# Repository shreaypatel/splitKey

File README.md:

# Ataraxia - Custom 50% Split Keyboard

### Description
Ataraxia is a wireless 52-key, 3D printed ergonomic keyboard desinged for a focused typing experience. The board is powered by dual Seeed Studio XIAO nRF52840 microcontrollers running ZMK firmware. 
It utilizes Bluetooth 5.0 to communicate seamlessly without a cable connecting the halves. The hardware stack includes a custom-routed printed circuit board, Kailh MX hotswap sockets, and direct-wired 
350mAh LiPo batteries for extended operational life.

This project was designed to create an open source, minimalist workspace that promotes ergonomic health withouting compromising functionality. Beyond the physical utility, it serves as a 
comprehensive hardware engineering exercise. Building this keyboard helped me learn engineering design, CAD modeling, PCB routing, soldering, and embedded firmware compilation. Check out the web app to learn touch typing on this split keyboard layout here: https://ataraxiatype.netlify.app/

3D Model

*Full mechanical assembly modeled in Onshape.*

Custom PCB

*Custom PCB designed and routed in KiCad.*

Wiring Diagram

*Simplified direct-wiring diagram connecting the 3.7V LiPo battery to the XIAO nRF52840.*

Bill of Materials (BOM)
[Click here to view the full Bill of Materials (CSV)](<BOM/splitkeyBOM - Sheet1.csv>)

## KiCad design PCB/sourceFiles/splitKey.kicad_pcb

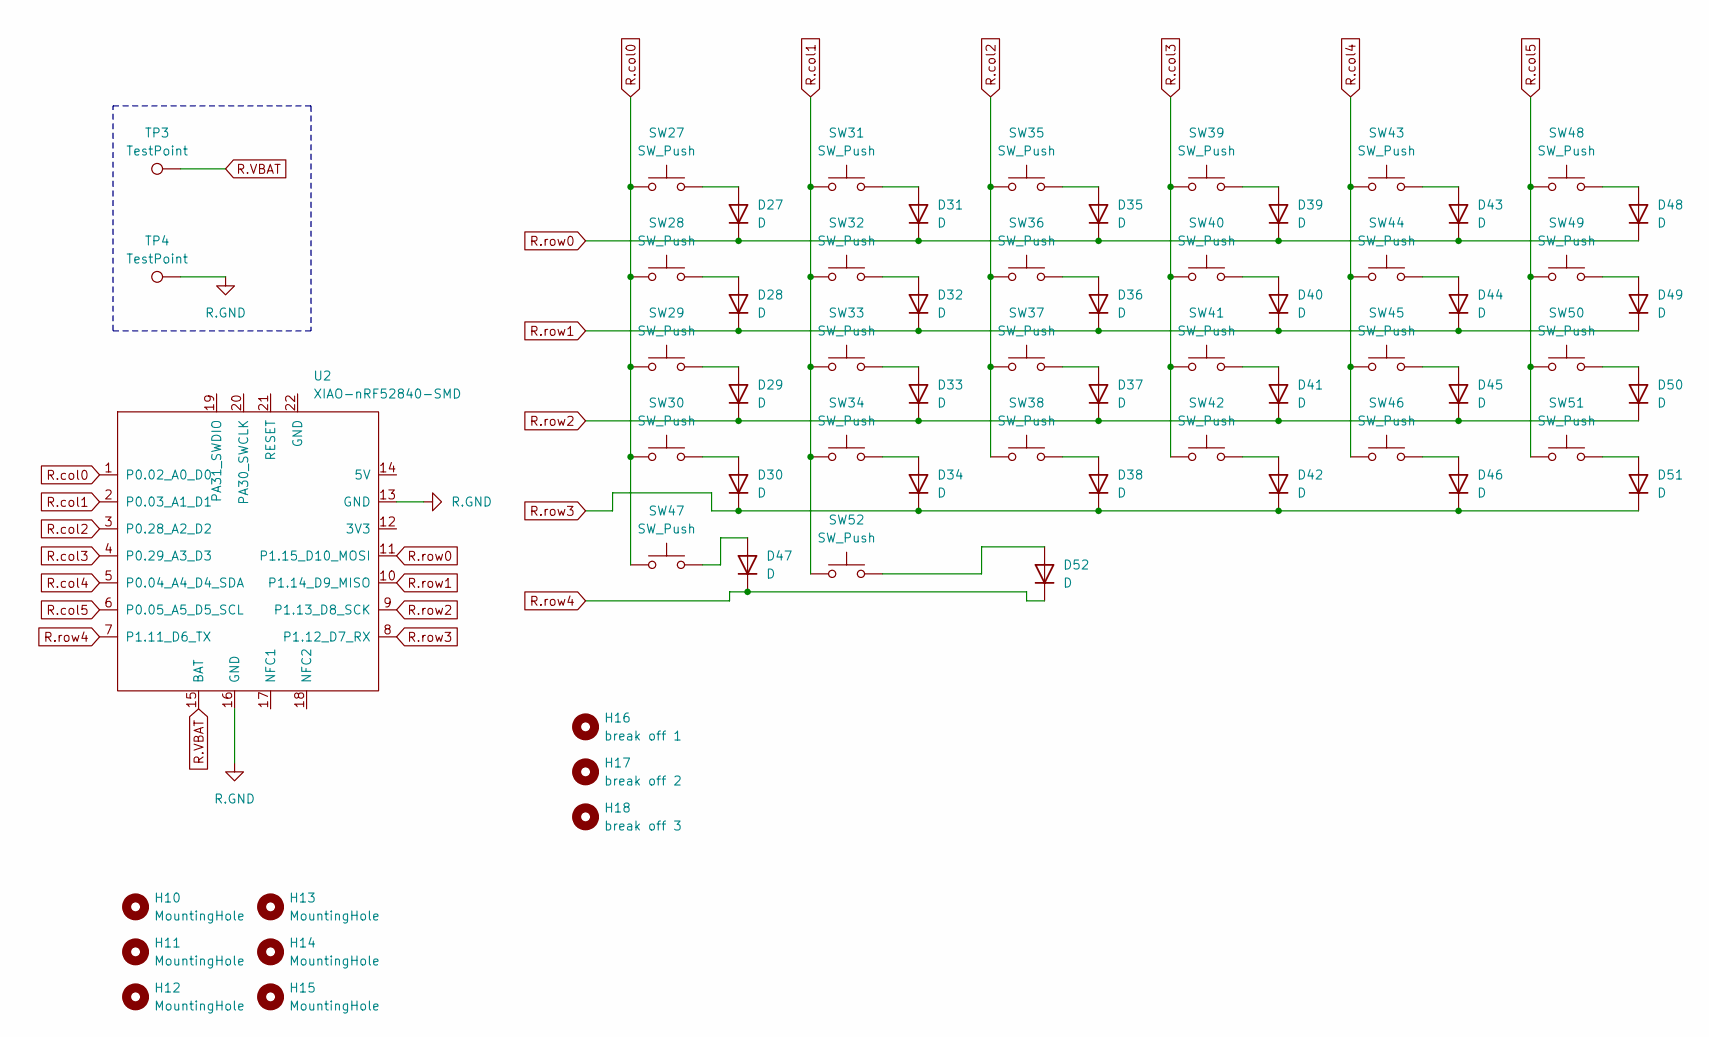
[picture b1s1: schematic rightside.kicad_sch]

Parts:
D27, D28, D29, D30, D31, D32, D33, D34, D35, D36, D37, D38, D39, D40, D41, D42, D43, D44, D45, D46, D47, D48, D49, D50, D51, D52: D; D_SOD-123
H10, H11, H12, H13, H14, H15: MountingHole; MountingHole_2.2mm_M2
H16: break off 1; mouse-bite-5mm-slot
H17: break off 2; mouse-bite-5mm-slot
H18: break off 3; mouse-bite-5mm-slot
SW27, SW28, SW29, SW30, SW31, SW32, SW33, SW34, SW35, SW36, SW37, SW38, SW39, SW40, SW41, SW42, SW43, SW44, SW45, SW46, SW47, SW48, SW49, SW50, SW51, SW52: SW_Push; MX_Hotswap_1.00u
TP3, TP4: TestPoint; TestPoint_Pad_D2.0mm
U2: XIAO-nRF52840-SMD; modified-XIAO-nRF52840-SMD

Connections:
unnamed: D27.2 (A), SW27.2
unnamed: D28.2 (A), SW28.2
unnamed: D29.2 (A), SW29.2
unnamed: D30.2 (A), SW30.2
unnamed: D31.2 (A), SW31.2
unnamed: D32.2 (A), SW32.2
unnamed: D33.2 (A), SW33.2
unnamed: D34.2 (A), SW34.2
unnamed: D35.2 (A), SW35.2
unnamed: D36.2 (A), SW36.2
unnamed: D37.2 (A), SW37.2
unnamed: D38.2 (A), SW38.2
unnamed: D39.2 (A), SW39.2
unnamed: D40.2 (A), SW40.2
unnamed: D41.2 (A), SW41.2
unnamed: D42.2 (A), SW42.2
unnamed: D43.2 (A), SW43.2
unnamed: D44.2 (A), SW44.2
unnamed: D45.2 (A), SW45.2
unnamed: D46.2 (A), SW46.2
unnamed: D47.2 (A), SW47.2
unnamed: D48.2 (A), SW48.2
unnamed: D49.2 (A), SW49.2
unnamed: D50.2 (A), SW50.2
unnamed: D51.2 (A), SW51.2
unnamed: D52.2 (A), SW52.2
R.GND: TP4.1 (1_1), U2.13 (GND), U2.16 (GND)
R.VBAT: TP3.1 (1_1), U2.15 (BAT)
R.col0: SW27.1, SW28.1, SW29.1, SW30.1, SW47.1, U2.1 (P0.02_A0_D0)
R.col1: SW31.1, SW32.1, SW33.1, SW34.1, SW52.1, U2.2 (P0.03_A1_D1)
R.col2: SW35.1, SW36.1, SW37.1, SW38.1, U2.3 (P0.28_A2_D2)
R.col3: SW39.1, SW40.1, SW41.1, SW42.1, U2.4 (P0.29_A3_D3)
R.col4: SW43.1, SW44.1, SW45.1, SW46.1, U2.5 (P0.04_A4_D4_SDA)
R.col5: SW48.1, SW49.1, SW50.1, SW51.1, U2.6 (P0.05_A5_D5_SCL)
R.row0: D27.1 (K), D31.1 (K), D35.1 (K), D39.1 (K), D43.1 (K), D48.1 (K), U2.11 (P1.15_D10_MOSI)
R.row1: D28.1 (K), D32.1 (K), D36.1 (K), D40.1 (K), D44.1 (K), D49.1 (K), U2.10 (P1.14_D9_MISO)
R.row2: D29.1 (K), D33.1 (K), D37.1 (K), D41.1 (K), D45.1 (K), D50.1 (K), U2.9 (P1.13_D8_SCK)
R.row3: D30.1 (K), D34.1 (K), D38.1 (K), D42.1 (K), D46.1 (K), D51.1 (K), U2.8 (P1.12_D7_RX)
R.row4: D47.1 (K), D52.1 (K), U2.7 (P1.11_D6_TX)

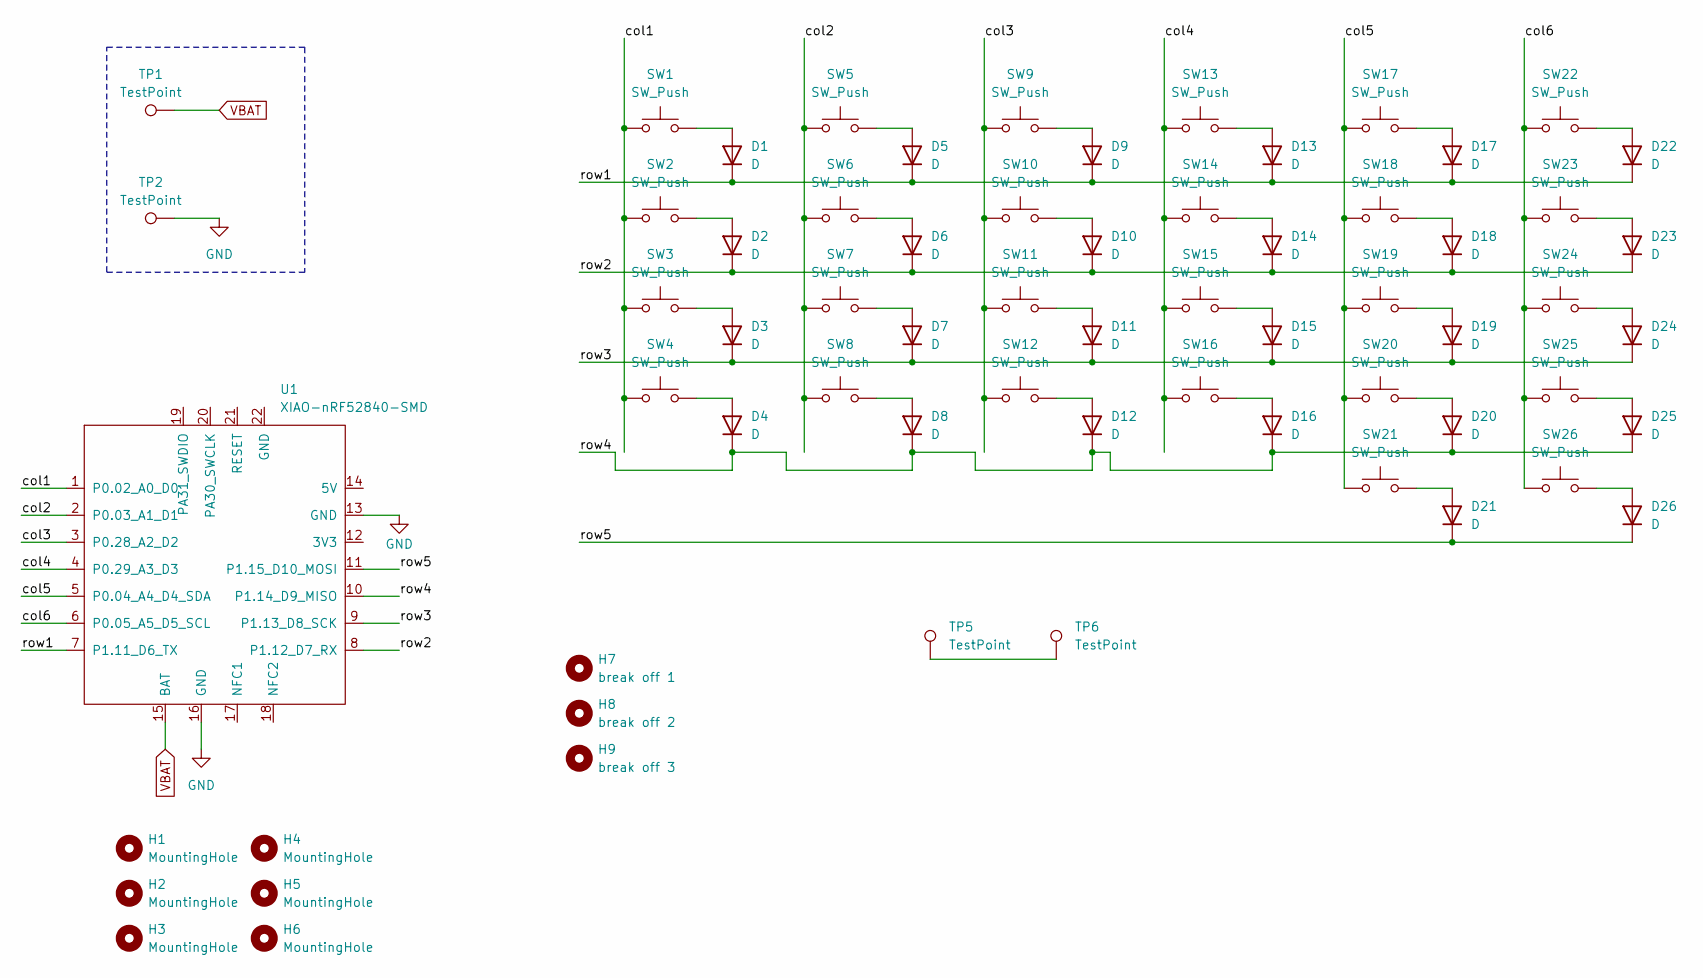
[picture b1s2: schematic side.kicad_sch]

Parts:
D1, D2, D3, D4, D5, D6, D7, D8, D9, D10, D11, D12, D13, D14, D15, D16, D17, D18, D19, D20, D21, D22, D23, D24, D25, D26: D; D_SOD-123
H1, H2, H3, H4, H5, H6: MountingHole; MountingHole_2.2mm_M2
H7: break off 1; mouse-bite-5mm-slot
H8: break off 2; mouse-bite-5mm-slot
H9: break off 3; mouse-bite-5mm-slot
SW1, SW2, SW3, SW4, SW5, SW6, SW7, SW8, SW9, SW10, SW11, SW12, SW13, SW14, SW15, SW16, SW17, SW18, SW19, SW20, SW21, SW22, SW23, SW24, SW25, SW26: SW_Push; MX_Hotswap_1.00u
TP1, TP2: TestPoint; TestPoint_Pad_D2.0mm
TP5, TP6: TestPoint; TestPoint_Pad_1.0x1.0mm
U1: XIAO-nRF52840-SMD; modified-XIAO-nRF52840-SMD

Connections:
/left/col1: SW1.1, SW2.1, SW3.1, SW4.1, U1.1 (P0.02_A0_D0)
/left/col2: SW5.1, SW6.1, SW7.1, SW8.1, U1.2 (P0.03_A1_D1)
/left/col3: SW9.1, SW10.1, SW11.1, SW12.1, U1.3 (P0.28_A2_D2)
/left/col4: SW13.1, SW14.1, SW15.1, SW16.1, U1.4 (P0.29_A3_D3)
/left/col5: SW17.1, SW18.1, SW19.1, SW20.1, SW21.1, U1.5 (P0.04_A4_D4_SDA)
/left/col6: SW22.1, SW23.1, SW24.1, SW25.1, SW26.1, U1.6 (P0.05_A5_D5_SCL)
/left/row1: D1.1 (K), D5.1 (K), D9.1 (K), D13.1 (K), D17.1 (K), D22.1 (K), U1.7 (P1.11_D6_TX)
/left/row2: D2.1 (K), D6.1 (K), D10.1 (K), D14.1 (K), D18.1 (K), D23.1 (K), U1.8 (P1.12_D7_RX)
/left/row3: D3.1 (K), D7.1 (K), D11.1 (K), D15.1 (K), D19.1 (K), D24.1 (K), U1.9 (P1.13_D8_SCK)
/left/row4: D4.1 (K), D8.1 (K), D12.1 (K), D16.1 (K), D20.1 (K), D25.1 (K), U1.10 (P1.14_D9_MISO)
/left/row5: D21.1 (K), D26.1 (K), U1.11 (P1.15_D10_MOSI)
GND: TP2.1 (1_1), U1.13 (GND), U1.16 (GND)
unnamed: D1.2 (A), SW1.2
unnamed: D2.2 (A), SW2.2
unnamed: D3.2 (A), SW3.2
unnamed: D4.2 (A), SW4.2
unnamed: D5.2 (A), SW5.2
unnamed: D6.2 (A), SW6.2
unnamed: D7.2 (A), SW7.2
unnamed: D8.2 (A), SW8.2
unnamed: D9.2 (A), SW9.2
unnamed: D10.2 (A), SW10.2
unnamed: D11.2 (A), SW11.2
unnamed: D12.2 (A), SW12.2
unnamed: D13.2 (A), SW13.2
unnamed: D14.2 (A), SW14.2
unnamed: D15.2 (A), SW15.2
unnamed: D16.2 (A), SW16.2
unnamed: D17.2 (A), SW17.2
unnamed: D18.2 (A), SW18.2
unnamed: D19.2 (A), SW19.2
unnamed: D20.2 (A), SW20.2
unnamed: D21.2 (A), SW21.2
unnamed: D22.2 (A), SW22.2
unnamed: D23.2 (A), SW23.2
unnamed: D24.2 (A), SW24.2
unnamed: D25.2 (A), SW25.2
unnamed: D26.2 (A), SW26.2
unnamed: TP5.1 (1_1), TP6.1 (1_1)
VBAT: TP1.1 (1_1), U1.15 (BAT)

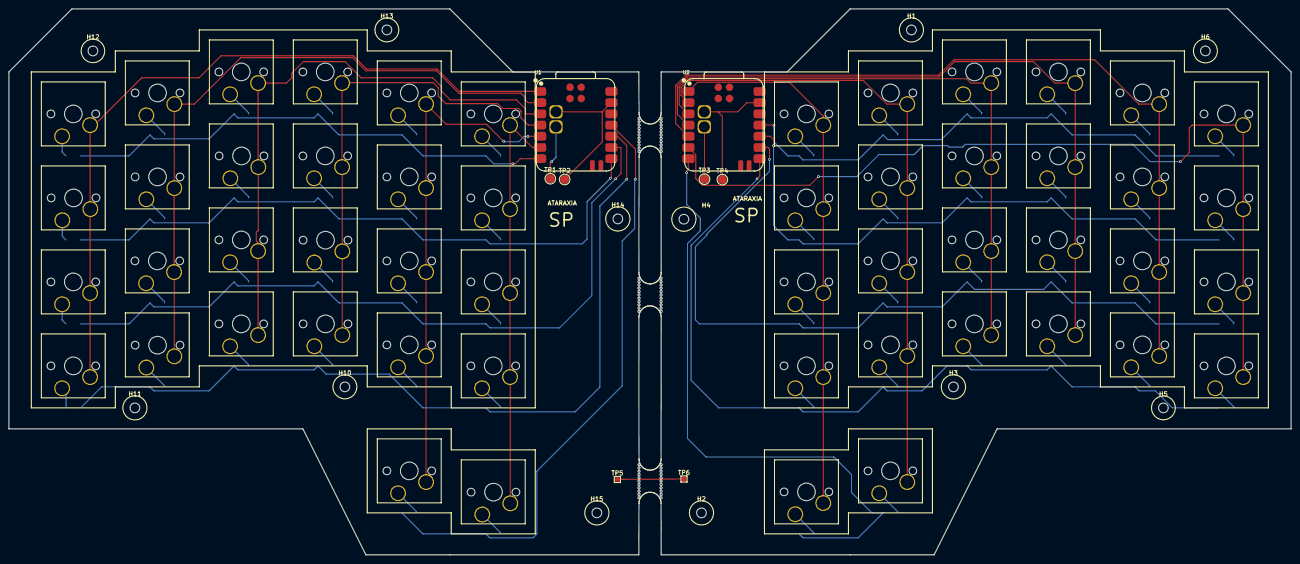
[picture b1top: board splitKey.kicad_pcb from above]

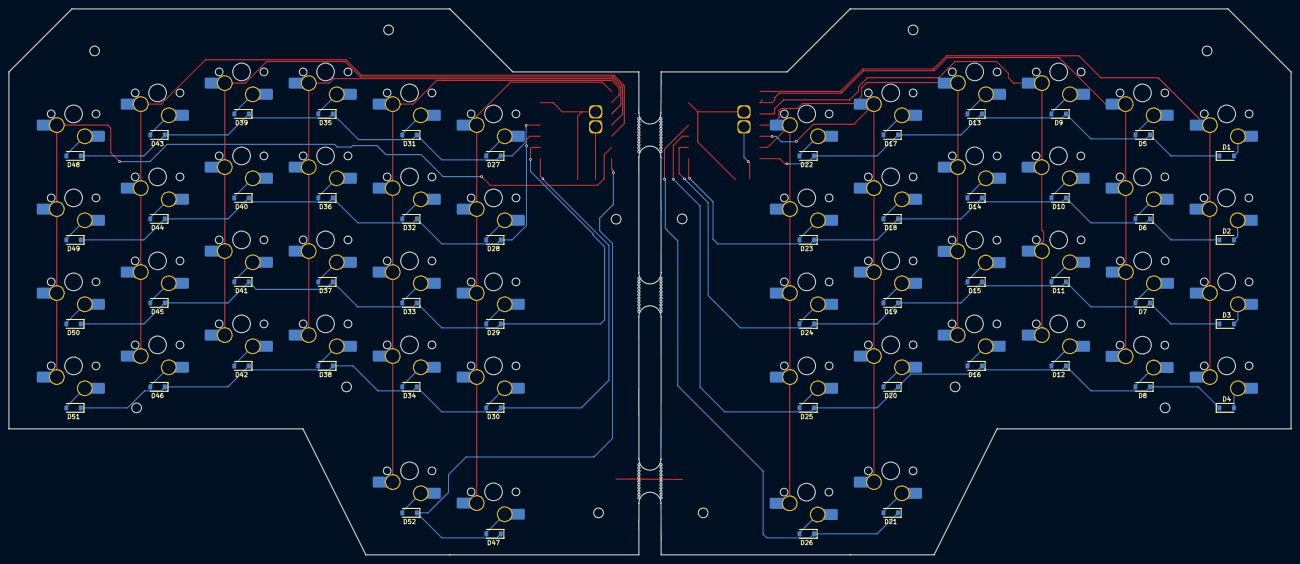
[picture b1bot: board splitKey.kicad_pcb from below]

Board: 2 copper layers, 290.8 x 123.8 mm, 127 parts (104 on the bottom side), 79 nets.

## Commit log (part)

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2026-04-26 iniital commit for Ataraxia split keyboard
2026-04-27 upadated BOM
2026-04-27 Create README for Ataraxia keyboard project
    Added detailed project description, images, and BOM.
2026-04-27 versionUpdate
2026-04-27 updated files
2026-05-01 added misisng hierarchal files
